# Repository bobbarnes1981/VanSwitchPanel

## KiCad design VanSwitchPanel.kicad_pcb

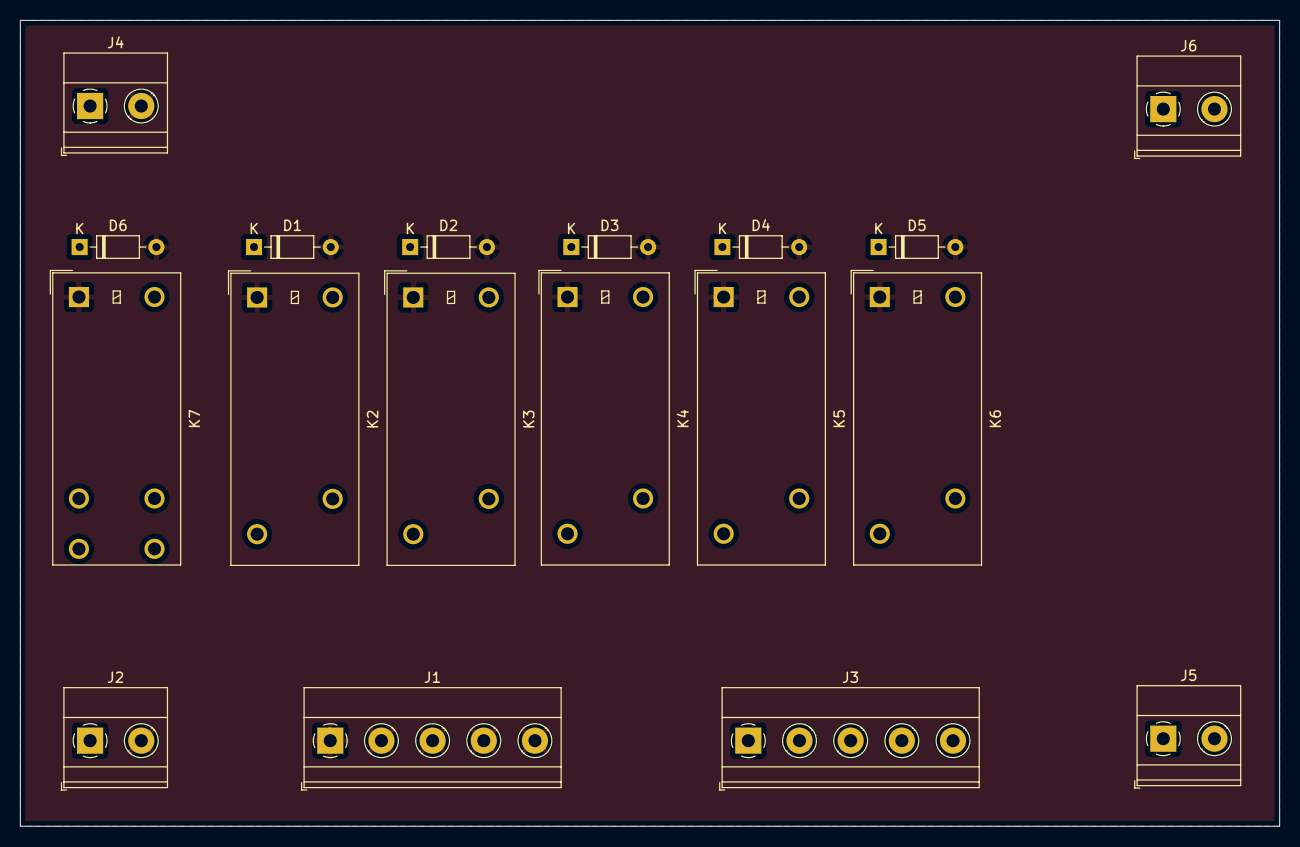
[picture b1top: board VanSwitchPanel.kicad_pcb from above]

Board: 2 copper layers, 125.0 x 80.0 mm, 18 parts (0 on the bottom side), 15 nets, no tracks yet.

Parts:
D1, D2, D3, D4, D5, D6: 1N4148; D_DO-35_SOD27_P7.62mm_Horizontal
J1, J3: Screw_Terminal_01x05; TerminalBlock_Phoenix_MKDS-1,5-5-5.08_1x05_P5.08mm_Horizont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
J2, J4, J5, J6: Screw_Terminal_01x02; TerminalBlock_Phoenix_MKDS-1,5-2-5.08_1x02_P5.08mm_Horizont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
K2, K3, K4, K5, K6: Relay_SPST-NO; Relay_SPST_Omron_G2RL-1A
K7: Relay_DPST-NO; Relay_DPST_Omron_G2RL-2A

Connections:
-BATT: J5.2, J6.2
/+12v Sw: J4.1, K7.24
/+BATT Sw: J6.1, K7.14
/OUT_1: J3.1, K2.14
/OUT_2: J3.2, K3.14
/OUT_3: J3.3, K4.14
/OUT_4: J3.4, K5.14
/OUT_5: J3.5, K6.14
GND: D1.2 (A), D2.2 (A), D3.2 (A), D4.2 (A), D5.2 (A), D6.2 (A), J1.1, J1.2, J1.3, J1.4, J1.5, J2.2, J4.2, K2.A1, K3.A1, K4.A1, K5.A1, K6.A1, K7.A1
unnamed: D1.1 (K), K2.A2
unnamed: D2.1 (K), K3.A2
unnamed: D3.1 (K), K4.A2
unnamed: D4.1 (K), K5.A2
unnamed: D5.1 (K), K6.A2
unnamed: D6.1 (K), K7.A2

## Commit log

2025-01-22 Add switched supply voltages
2025-01-22 Do not feed all supplies through main relay
2025-01-24 Add pcb and footprints
